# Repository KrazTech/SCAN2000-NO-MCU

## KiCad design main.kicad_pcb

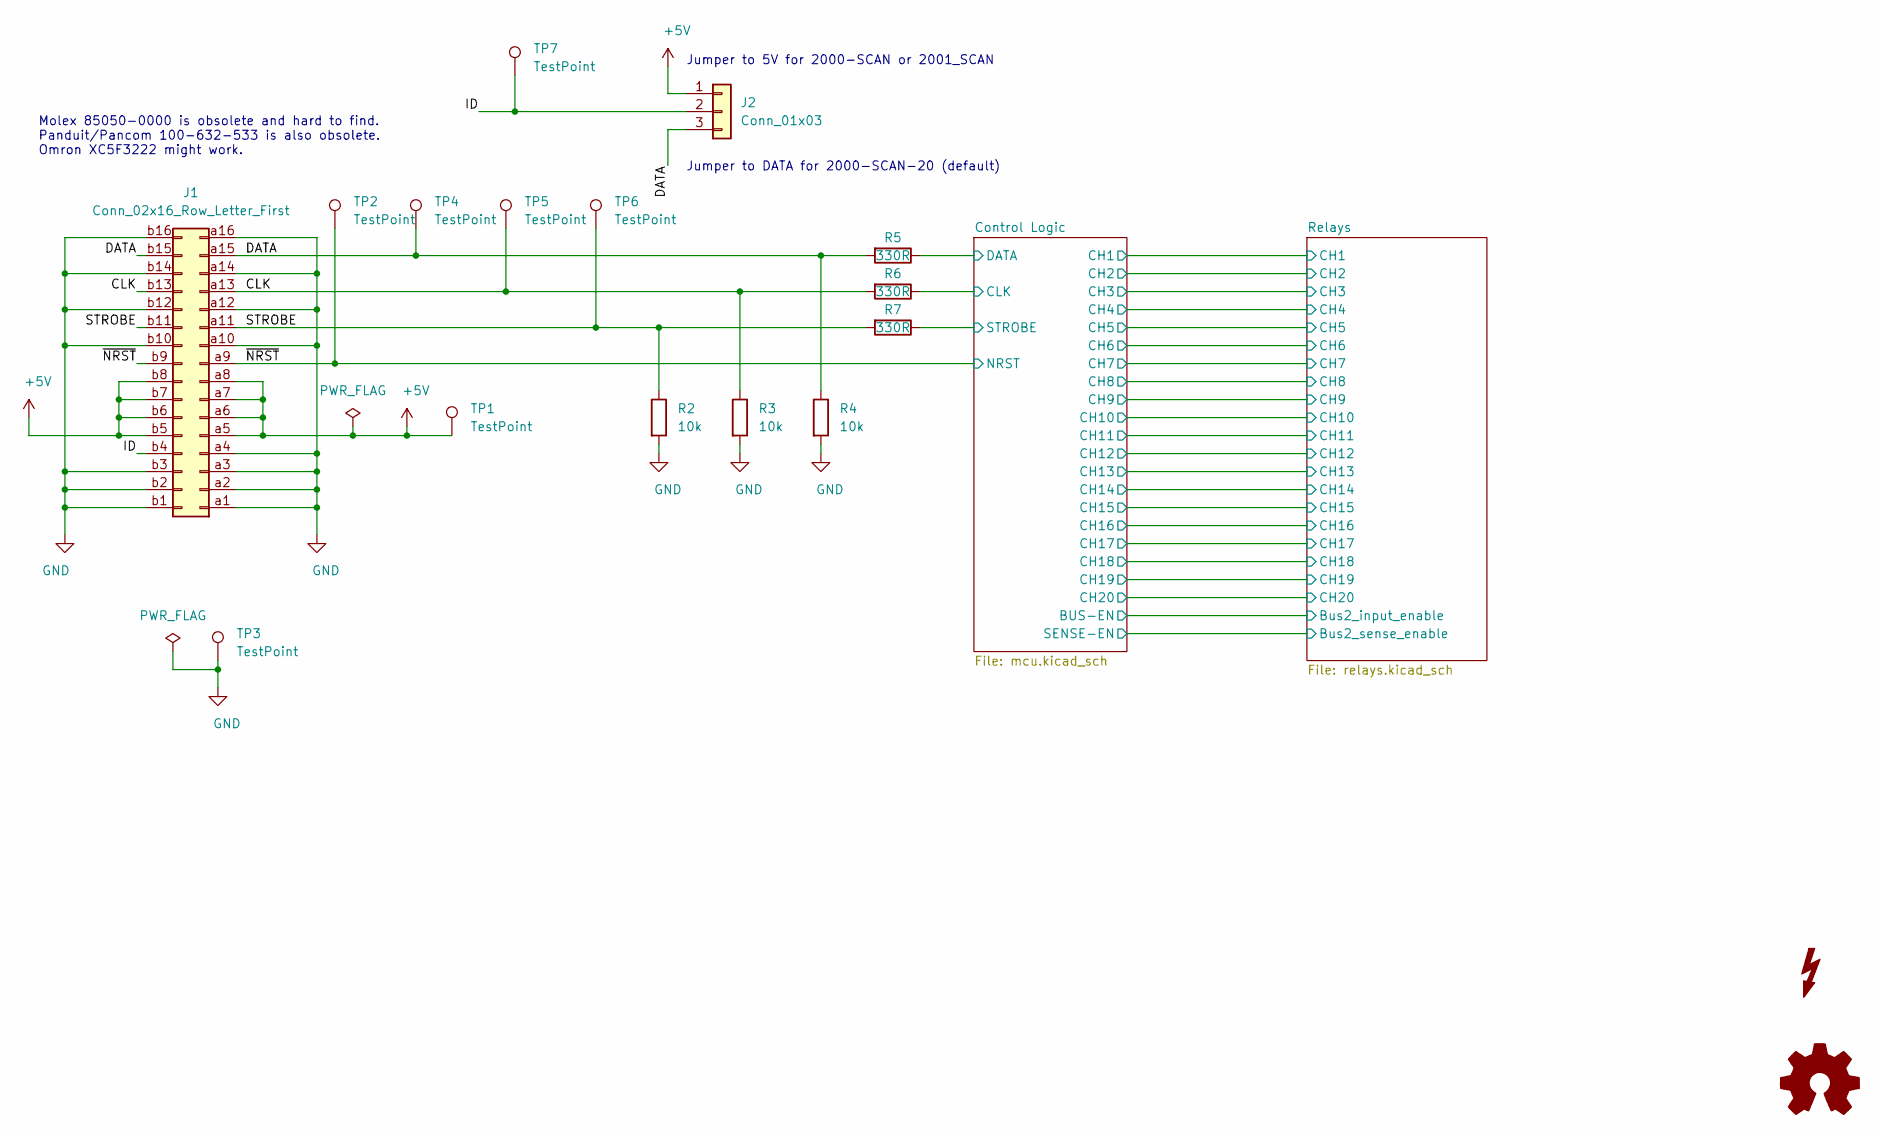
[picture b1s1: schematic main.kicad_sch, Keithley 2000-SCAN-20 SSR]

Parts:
J1: Conn_02x16_Row_Letter_First; DIN41612_B2_2x16_Male_Horizontal_THT
J2: Conn_01x03; PinHeader_1x03_P2.54mm_Vertical
LOGO2: Logo_Open_Hardware_Small; OSHW-Logo_7.5x8mm_SilkScreen
R2, R3, R4: 10k; R_0603_1608Metric
R5, R6, R7: 330R; R_0603_1608Metric
SYM1: SYM_Flash_Small; Symbol_Highvoltage_Type2_CopperTop_Small
TP1, TP2, TP3, TP4, TP5, TP6, TP7: TestPoint; TestPoint_Loop_D2.60mm_Drill1.6mm_Beaded

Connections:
+5V: J1.a5, J1.a6, J1.a7, J1.a8, J1.b5, J1.b6, J1.b7, J1.b8, J2.1, TP1.1; also elsewhere on the board
/CLK: J1.a13, J1.b13, R3.1, R6.2, TP5.1
/Control Logic/CLK: R6.1; also elsewhere on the board
/Control Logic/DATA: R5.1; also elsewhere on the board
/Control Logic/STROBE: R7.1; also elsewhere on the board
/DATA: J1.a15, J1.b15, J2.3, R4.1, R5.2, TP4.1
/ID: J1.b4, J2.2, TP7.1
/STROBE: J1.a11, J1.b11, R2.1, R7.2, TP6.1
/~NRST: J1.a9, J1.b9, TP2.1; also elsewhere on the board
GND: J1.a1, J1.a2, J1.a3, J1.a4, J1.a10, J1.a12, J1.a14, J1.a16, J1.b1, J1.b2, J1.b3, J1.b10, J1.b12, J1.b14, J1.b16, R2.2, R3.2, R4.2, TP3.1; also elsewhere on the board

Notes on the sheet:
Jumper to 5V for 2000-SCAN or 2001_SCAN
Molex 85050-0000 is obsolete and hard to find. Panduit/Pancom 100-632-533 is also obsolete. Omron XC5F3222 might work.
Jumper to DATA for 2000-SCAN-20 (default)

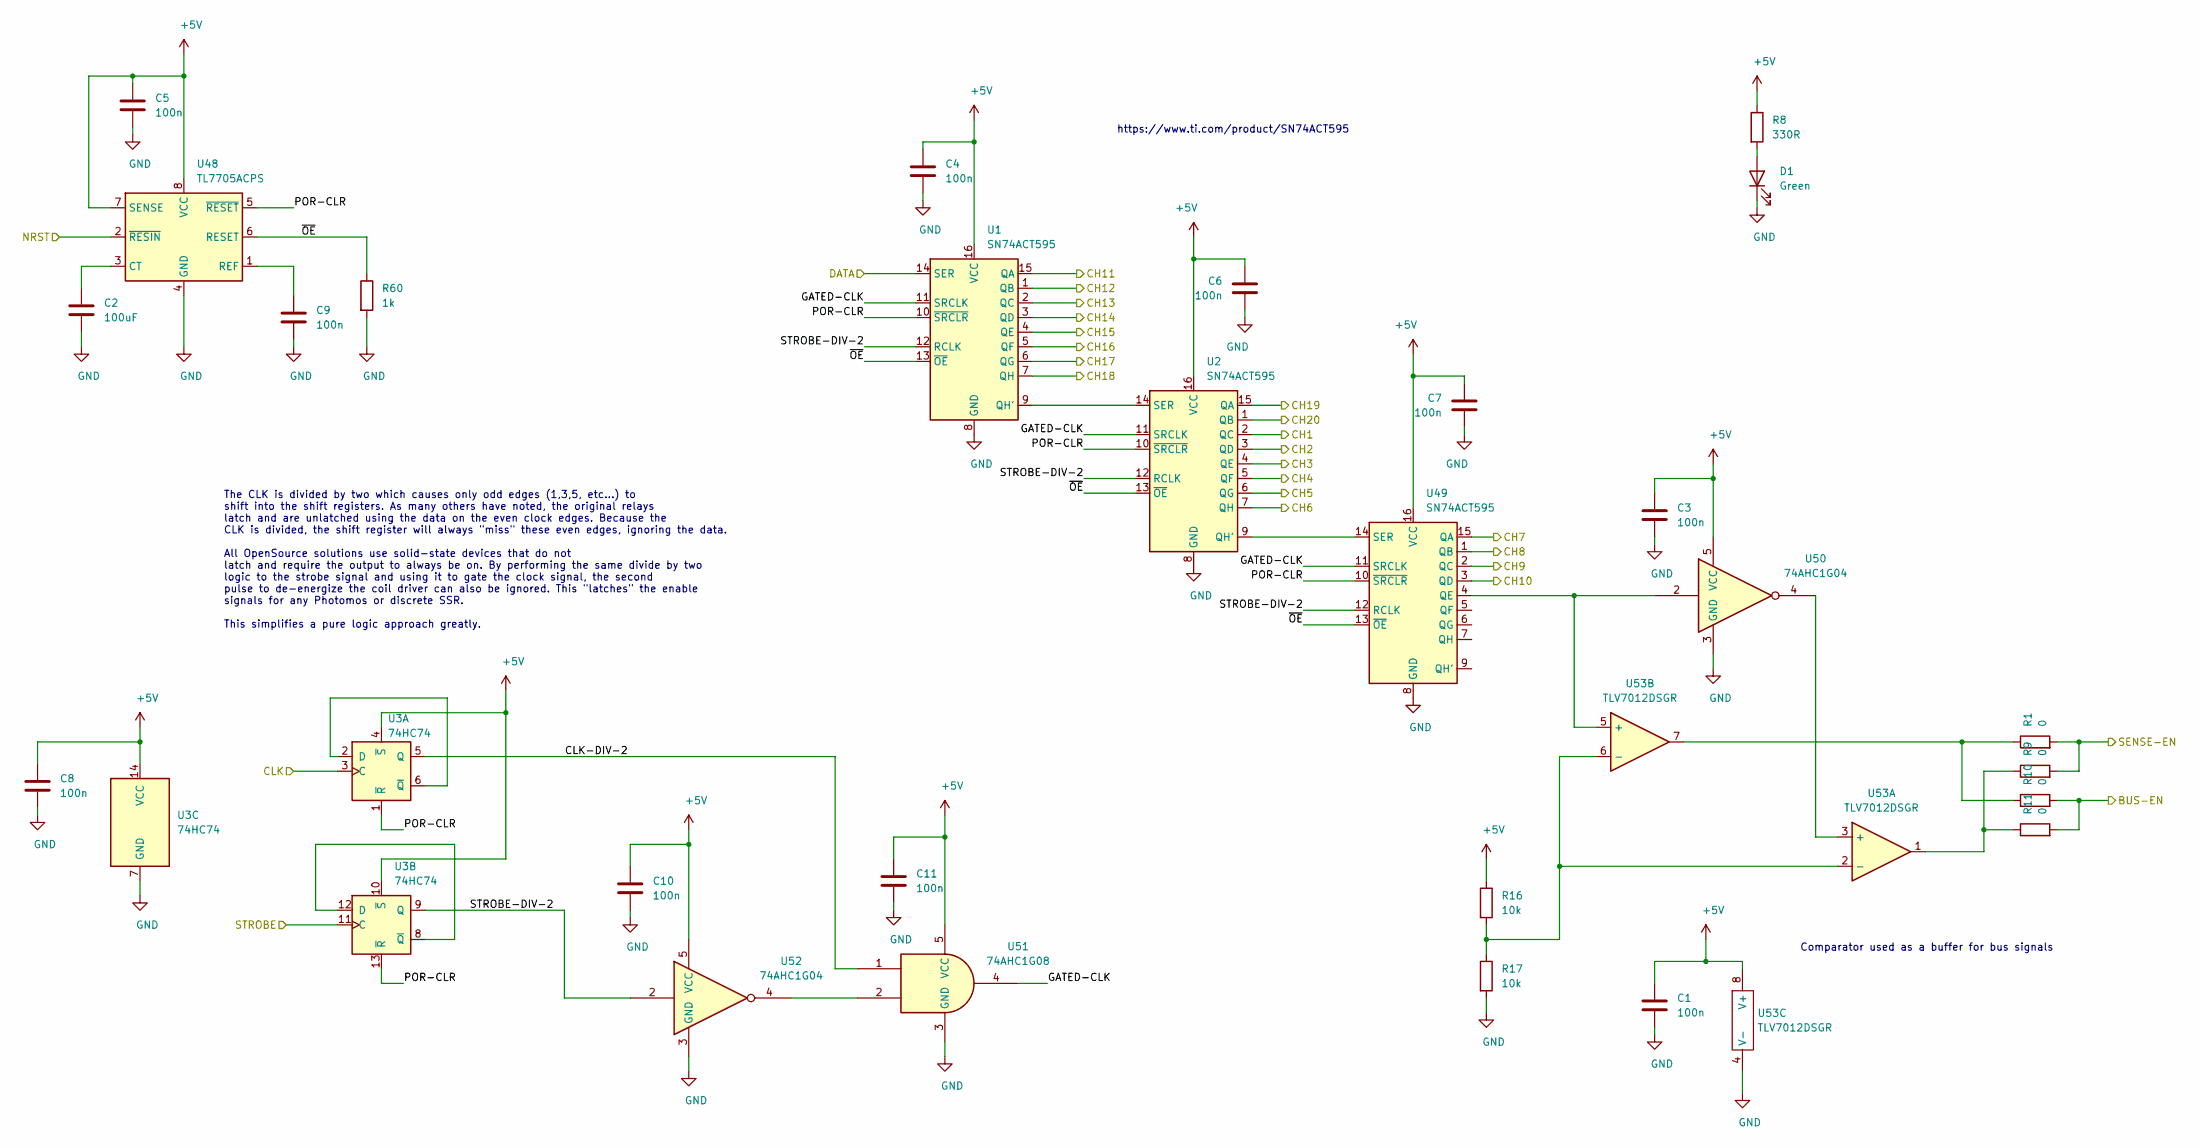
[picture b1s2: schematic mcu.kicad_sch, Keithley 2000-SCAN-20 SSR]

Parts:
C1, C3, C4, C5, C6, C7, C8, C9, C10, C11: 100n; C_0603_1608Metric
C2: 100uF; C_0603_1608Metric
D1: Green; LED_0603_1608Metric
R1, R9, R10, R11: 0; R_0603_1608Metric
R8: 330R; R_0603_1608Metric
R16, R17: 10k; R_0603_1608Metric
R60: 1k; R_0603_1608Metric
U1, U2, U49: SN74ACT595; TSSOP-16_4.4x5mm_P0.65mm
U3: 74HC74; TSSOP-14_4.4x5mm_P0.65mm
U48: TL7705ACPS; SOIC-8_5.3x6.2mm_P1.27mm
U50, U52: 74AHC1G04; SOT-553
U51: 74AHC1G08; SOT-553
U53: TLV7012DSGR; Texas_DSG0008A_WSON-8-1EP_2x2mm_P0.5mm_EP0.9x1.6mm_ThermalV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

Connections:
+5V: C1.1, C3.1, C4.1, C5.1, C6.1, C7.1, C8.1, C10.1, C11.1, R8.1, R16.1, U1.16 (VCC), U2.16 (VCC), U3.4 (~S), U3.10 (~S), U3.14 (VCC), U48.7 (SENSE), U48.8 (VCC), U49.16 (VCC), U50.5 (VCC), U51.5 (VCC), U52.5 (VCC), U53.8 (V+); also elsewhere on the board
/Control Logic/BUS-EN: R10.2, R11.2; also elsewhere on the board
/Control Logic/CH1: U2.2 (QC); also elsewhere on the board
/Control Logic/CH2: U2.3 (QD); also elsewhere on the board
/Control Logic/CH3: U2.4 (QE); also elsewhere on the board
/Control Logic/CH4: U2.5 (QF); also elsewhere on the board
/Control Logic/CH5: U2.6 (QG); also elsewhere on the board
/Control Logic/CH6: U2.7 (QH); also elsewhere on the board
/Control Logic/CH7: U49.15 (QA); also elsewhere on the board
/Control Logic/CH8: U49.1 (QB); also elsewhere on the board
/Control Logic/CH9: U49.2 (QC); also elsewhere on the board
/Control Logic/CH10: U49.3 (QD); also elsewhere on the board
/Control Logic/CH11: U1.15 (QA); also elsewhere on the board
/Control Logic/CH12: U1.1 (QB); also elsewhere on the board
/Control Logic/CH13: U1.2 (QC); also elsewhere on the board
/Control Logic/CH14: U1.3 (QD); also elsewhere on the board
/Control Logic/CH15: U1.4 (QE); also elsewhere on the board
/Control Logic/CH16: U1.5 (QF); also elsewhere on the board
/Control Logic/CH17: U1.6 (QG); also elsewhere on the board
/Control Logic/CH18: U1.7 (QH); also elsewhere on the board
/Control Logic/CH19: U2.15 (QA); also elsewhere on the board
/Control Logic/CH20: U2.1 (QB); also elsewhere on the board
/Control Logic/CLK: U3.3 (C); also elsewhere on the board
/Control Logic/CLK-DIV-2: U3.5 (Q), U51.1
/Control Logic/DATA: U1.14 (SER); also elsewhere on the board
/Control Logic/GATED-CLK: U1.11 (SRCLK), U2.11 (SRCLK), U49.11 (SRCLK), U51.4
/Control Logic/POR-CLR: U1.10 (~SRCLR), U2.10 (~SRCLR), U3.1 (~R), U3.13 (~R), U48.5 (~RESET), U49.10 (~SRCLR)
/Control Logic/SENSE-EN: R1.2, R9.2; also elsewhere on the board
/Control Logic/STROBE: U3.11 (C); also elsewhere on the board
/Control Logic/STROBE-DIV-2: U1.12 (RCLK), U2.12 (RCLK), U3.9 (Q), U49.12 (RCLK), U52.2
/Control Logic/~OE: R60.1, U1.13 (~OE), U2.13 (~OE), U48.6 (RESET), U49.13 (~OE)
/~NRST: U48.2 (~RESIN); also elsewhere on the board
GND: C1.2, C2.2, C3.2, C4.2, C5.2, C6.2, C7.2, C8.2, C9.2, C10.2, C11.2, D1.1 (K), R17.2, R60.2, U1.8 (GND), U2.8 (GND), U3.7 (GND), U48.4 (GND), U49.8 (GND), U50.3 (GND), U51.3 (GND), U52.3 (GND), U53.4 (V-); also elsewhere on the board
unnamed: D1.2 (A), R8.2
unnamed: R1.1, R10.1, U53.7
unnamed: R9.1, R11.1, U53.1
unnamed: U1.9 (QH'), U2.14 (SER)
unnamed: U2.9 (QH'), U49.14 (SER)
unnamed: U3.2 (D), U3.6 (~Q)
unnamed: U3.8 (~Q), U3.12 (D)
unnamed: C2.1, U48.3 (CT)
unnamed: C9.1, U48.1 (REF)
unnamed: U49.4 (QE), U50.2, U53.5 (+)
unnamed: U51.2, U52.4
unnamed: U50.4, U53.3 (+)
unnamed: R16.2, R17.1, U53.2 (-), U53.6 (-)

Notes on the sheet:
The CLK is divided by two which causes only odd edges (1,3,5, etc...) to shift into the shift registers. As many others have noted, the original relays latch and are unlatched using the data on the even clock edges. Because the CLK is divided, the shift register will always "miss" these even edges,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
https://www.ti.com/product/SN74ACT595
Comparator used as a buffer for bus signals

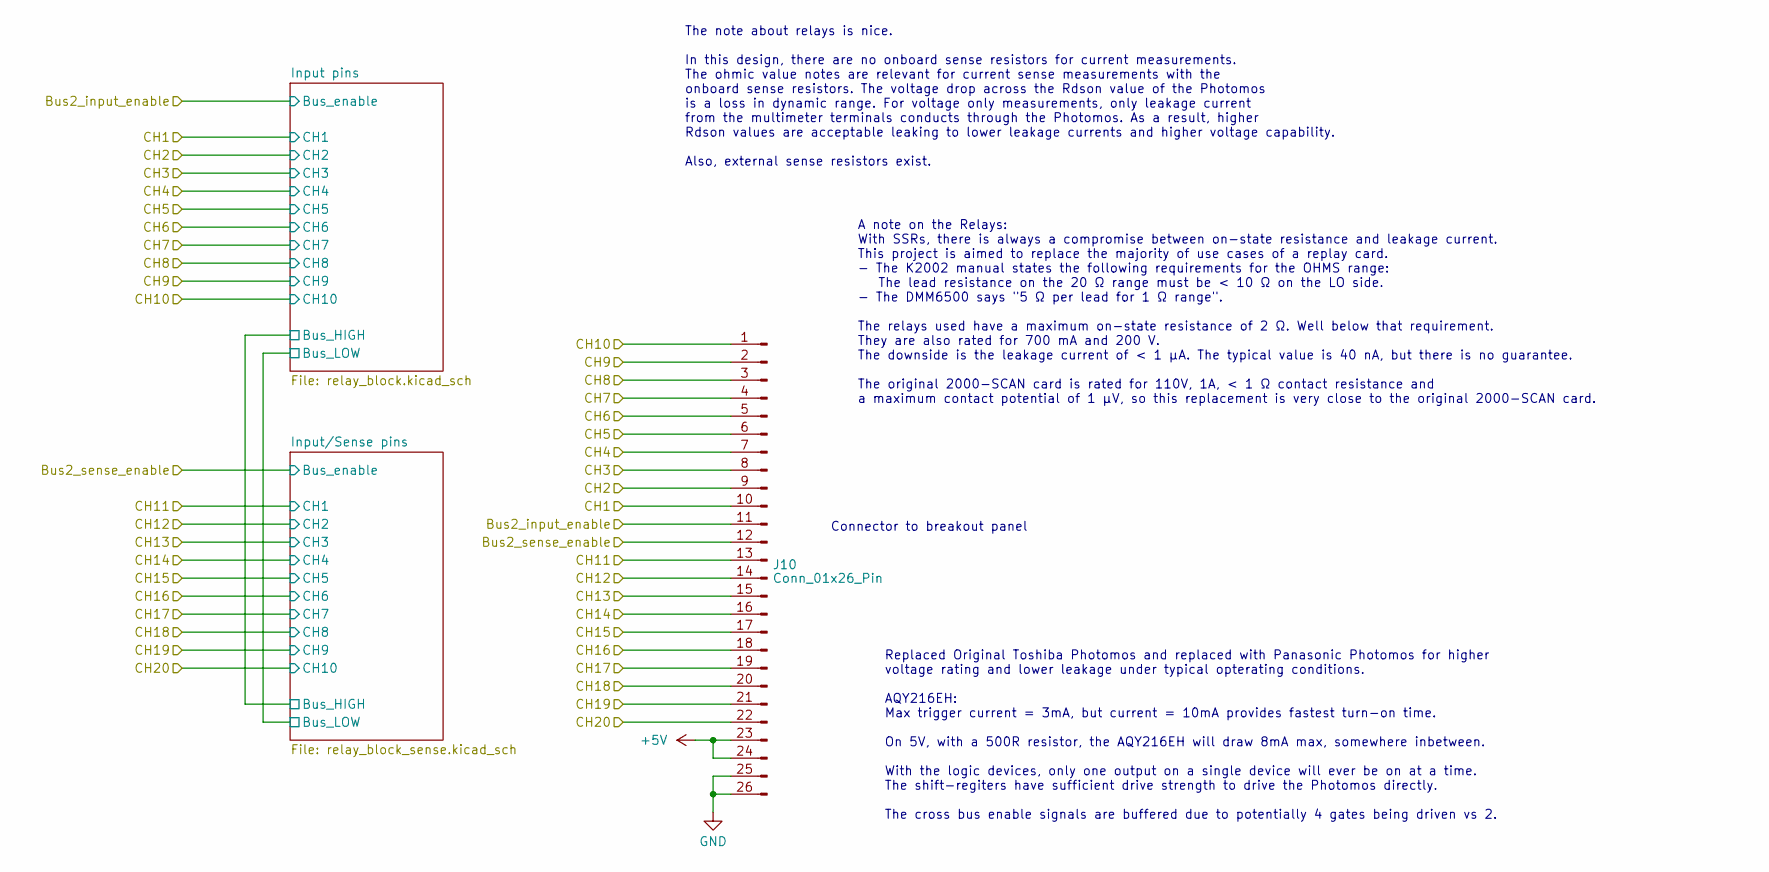
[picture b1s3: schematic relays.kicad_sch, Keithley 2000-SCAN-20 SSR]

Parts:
J10: Conn_01x26_Pin; IDC-Header_2x13_P2.54mm_Latch_Horizontal

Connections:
+5V: J10.23, J10.24; also elsewhere on the board
/Control Logic/BUS-EN: J10.11; also elsewhere on the board
/Control Logic/CH1: J10.10; also elsewhere on the board
/Control Logic/CH2: J10.9; also elsewhere on the board
/Control Logic/CH3: J10.8; also elsewhere on the board
/Control Logic/CH4: J10.7; also elsewhere on the board
/Control Logic/CH5: J10.6; also elsewhere on the board
/Control Logic/CH6: J10.5; also elsewhere on the board
/Control Logic/CH7: J10.4; also elsewhere on the board
/Control Logic/CH8: J10.3; also elsewhere on the board
/Control Logic/CH9: J10.2; also elsewhere on the board
/Control Logic/CH10: J10.1; also elsewhere on the board
/Control Logic/CH11: J10.13; also elsewhere on the board
/Control Logic/CH12: J10.14; also elsewhere on the board
/Control Logic/CH13: J10.15; also elsewhere on the board
/Control Logic/CH14: J10.16; also elsewhere on the board
/Control Logic/CH15: J10.17; also elsewhere on the board
/Control Logic/CH16: J10.18; also elsewhere on the board
/Control Logic/CH17: J10.19; also elsewhere on the board
/Control Logic/CH18: J10.20; also elsewhere on the board
/Control Logic/CH19: J10.21; also elsewhere on the board
/Control Logic/CH20: J10.22; also elsewhere on the board
/Control Logic/SENSE-EN: J10.12; also elsewhere on the board
GND: J10.25, J10.26; also elsewhere on the board

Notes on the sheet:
A note on the Relays: With SSRs, there is always a compromise between on-state resistance and leakage current. This project is aimed to replace the majority of use cases of a replay card. - The K2002 manual states the following requirements for the OHMS range: The lead resistance on the 20 Ω range 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
Replaced Original Toshiba Photomos and replaced with Panasonic Photomos for higher voltage rating and lower leakage under typical opterating conditions. AQY216EH: Max trigger current = 3mA, but current = 10mA provides fastest turn-on time. On 5V, with a 500R resistor, the AQY216EH will draw 8mA max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
The note about relays is nice. In this design, there are no onboard sense resistors for current measurements. The ohmic value notes are relevant for current sense measurements with the onboard sense resistors. The voltage drop across the Rdson value of the Photomos is a loss in dynamic range. For v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
Connector to breakout panel

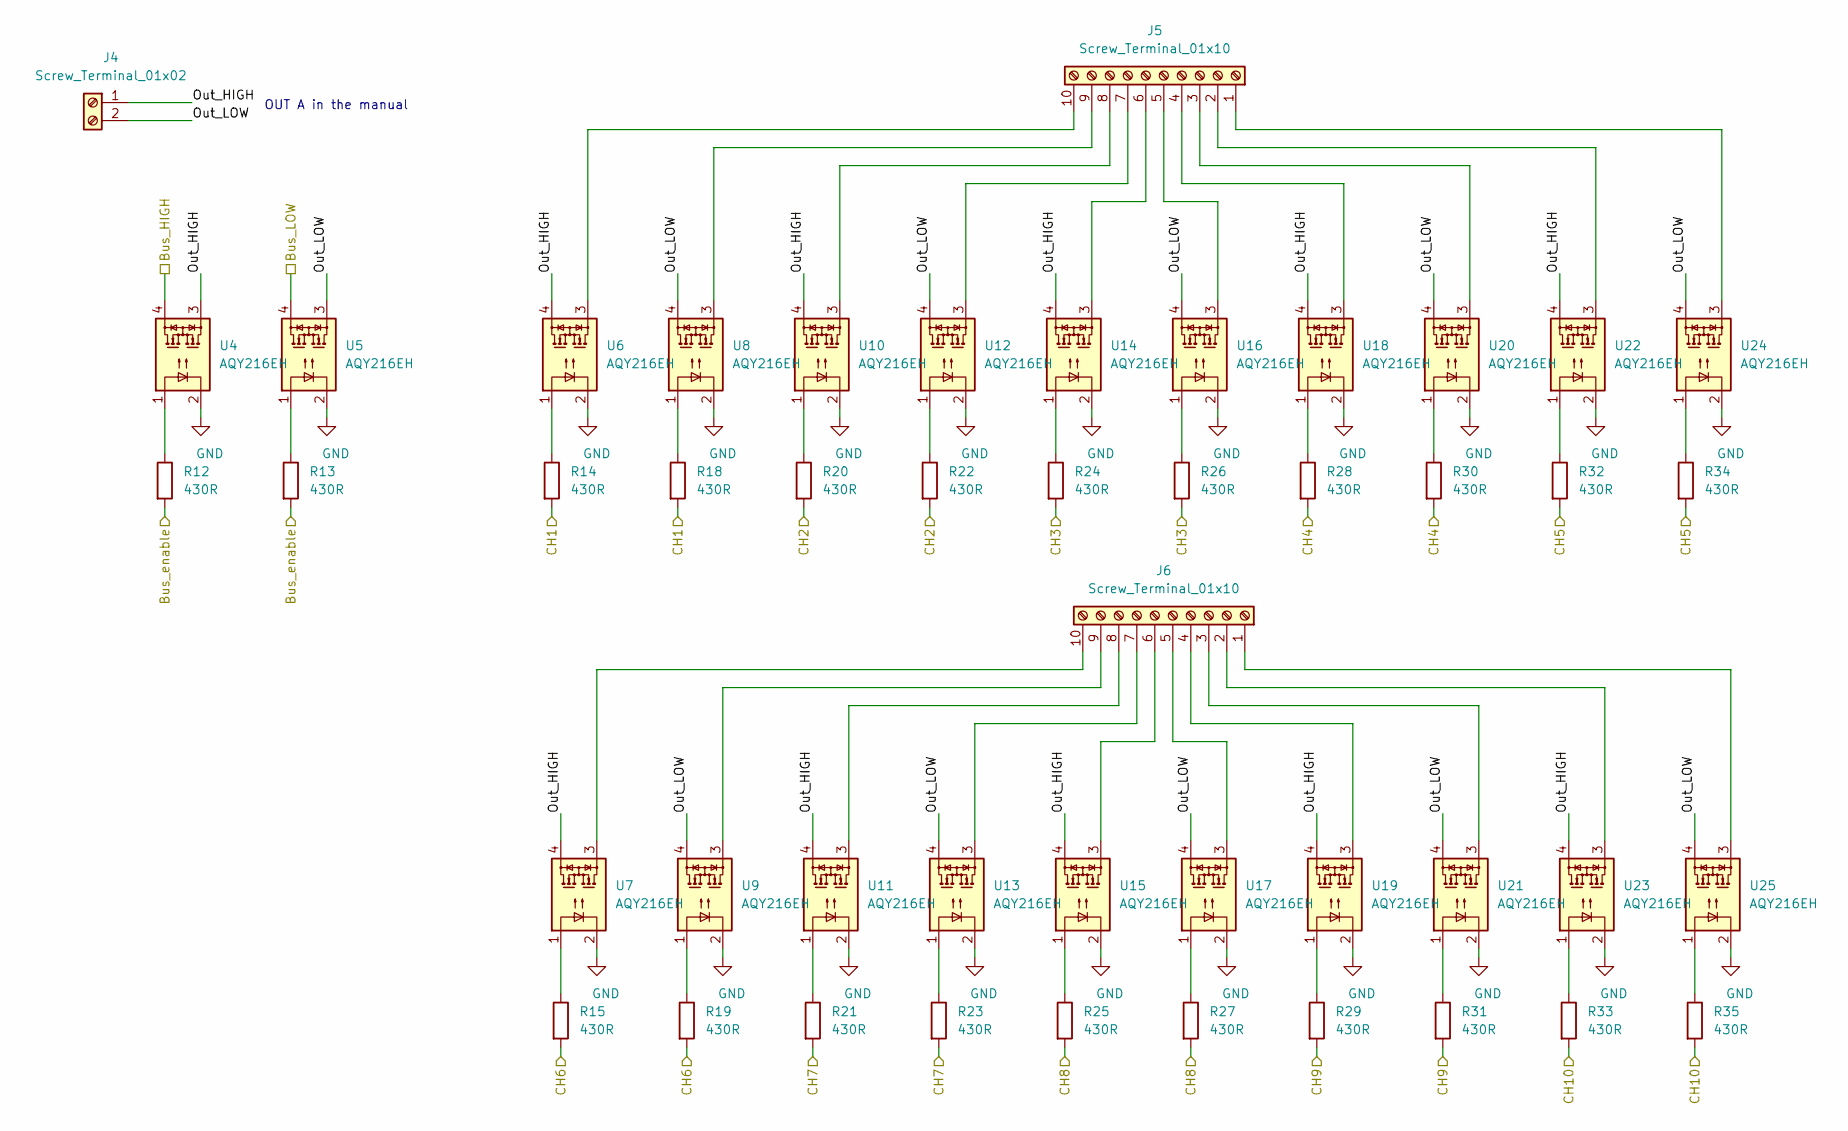
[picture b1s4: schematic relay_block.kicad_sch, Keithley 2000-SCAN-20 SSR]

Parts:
J4: Screw_Terminal_01x02; TerminalBlock_Phoenix_SMKDSN-1,5-2-5.08_1x02_P5.08mm_Horizo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
J5, J6: Screw_Terminal_01x10; TerminalBlock_Phoenix_SMKDSN-1,5-10-5.08_1x10_P5.08mm_Horiz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
R12, R13, R14, R15, R18, R19, R20, R21, R22, R23, R24, R25, R26, R27, R28, R29, R30, R31, R32, R33, R34, R35: 430R; R_0603_1608Metric
U4, U5, U6, U7, U8, U9, U10, U11, U12, U13, U14, U15, U16, U17, U18, U19, U20, U21, U22, U23, U24, U25: AQY216EH; DIP-4_W7.62mm_Least

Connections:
/Control Logic/BUS-EN: R12.2, R13.2; also elsewhere on the board
/Control Logic/CH1: R14.2, R18.2; also elsewhere on the board
/Control Logic/CH2: R20.2, R22.2; also elsewhere on the board
/Control Logic/CH3: R24.2, R26.2; also elsewhere on the board
/Control Logic/CH4: R28.2, R30.2; also elsewhere on the board
/Control Logic/CH5: R32.2, R34.2; also elsewhere on the board
/Control Logic/CH6: R15.2, R19.2; also elsewhere on the board
/Control Logic/CH7: R21.2, R23.2; also elsewhere on the board
/Control Logic/CH8: R25.2, R27.2; also elsewhere on the board
/Control Logic/CH9: R29.2, R31.2; also elsewhere on the board
/Control Logic/CH10: R33.2, R35.2; also elsewhere on the board
/Relays/Input pins/Bus_HIGH: U4.4; also elsewhere on the board
/Relays/Input pins/Bus_LOW: U5.4; also elsewhere on the board
/Relays/Input pins/Out_HIGH: J4.1, U4.3, U6.4, U7.4, U10.4, U11.4, U14.4, U15.4, U18.4, U19.4, U22.4, U23.4
/Relays/Input pins/Out_LOW: J4.2, U5.3, U8.4, U9.4, U12.4, U13.4, U16.4, U17.4, U20.4, U21.4, U24.4, U25.4
GND: U4.2, U5.2, U6.2, U7.2, U8.2, U9.2, U10.2, U11.2, U12.2, U13.2, U14.2, U15.2, U16.2, U17.2, U18.2, U19.2, U20.2, U21.2, U22.2, U23.2, U24.2, U25.2; also elsewhere on the board
unnamed: J5.1, U24.3
unnamed: J5.2, U22.3
unnamed: J5.3, U20.3
unnamed: J5.4, U18.3
unnamed: J5.5, U16.3
unnamed: J5.6, U14.3
unnamed: J5.7, U12.3
unnamed: J5.8, U10.3
unnamed: J5.9, U8.3
unnamed: J5.10, U6.3
unnamed: J6.1, U25.3
unnamed: J6.2, U23.3
unnamed: J6.3, U21.3
unnamed: J6.4, U19.3
unnamed: J6.5, U17.3
unnamed: J6.6, U15.3
unnamed: J6.7, U13.3
unnamed: J6.8, U11.3
unnamed: J6.9, U9.3
unnamed: J6.10, U7.3
unnamed: R12.1, U4.1
unnamed: R13.1, U5.1
unnamed: R14.1, U6.1
unnamed: R15.1, U7.1
unnamed: R18.1, U8.1
unnamed: R19.1, U9.1
unnamed: R20.1, U10.1
unnamed: R21.1, U11.1
unnamed: R22.1, U12.1
unnamed: R23.1, U13.1
unnamed: R24.1, U14.1
unnamed: R25.1, U15.1
unnamed: R26.1, U16.1
unnamed: R27.1, U17.1
unnamed: R28.1, U18.1
unnamed: R29.1, U19.1
unnamed: R30.1, U20.1
unnamed: R31.1, U21.1
unnamed: R32.1, U22.1
unnamed: R33.1, U23.1
unnamed: R34.1, U24.1
unnamed: R35.1, U25.1

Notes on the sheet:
OUT A in the manual

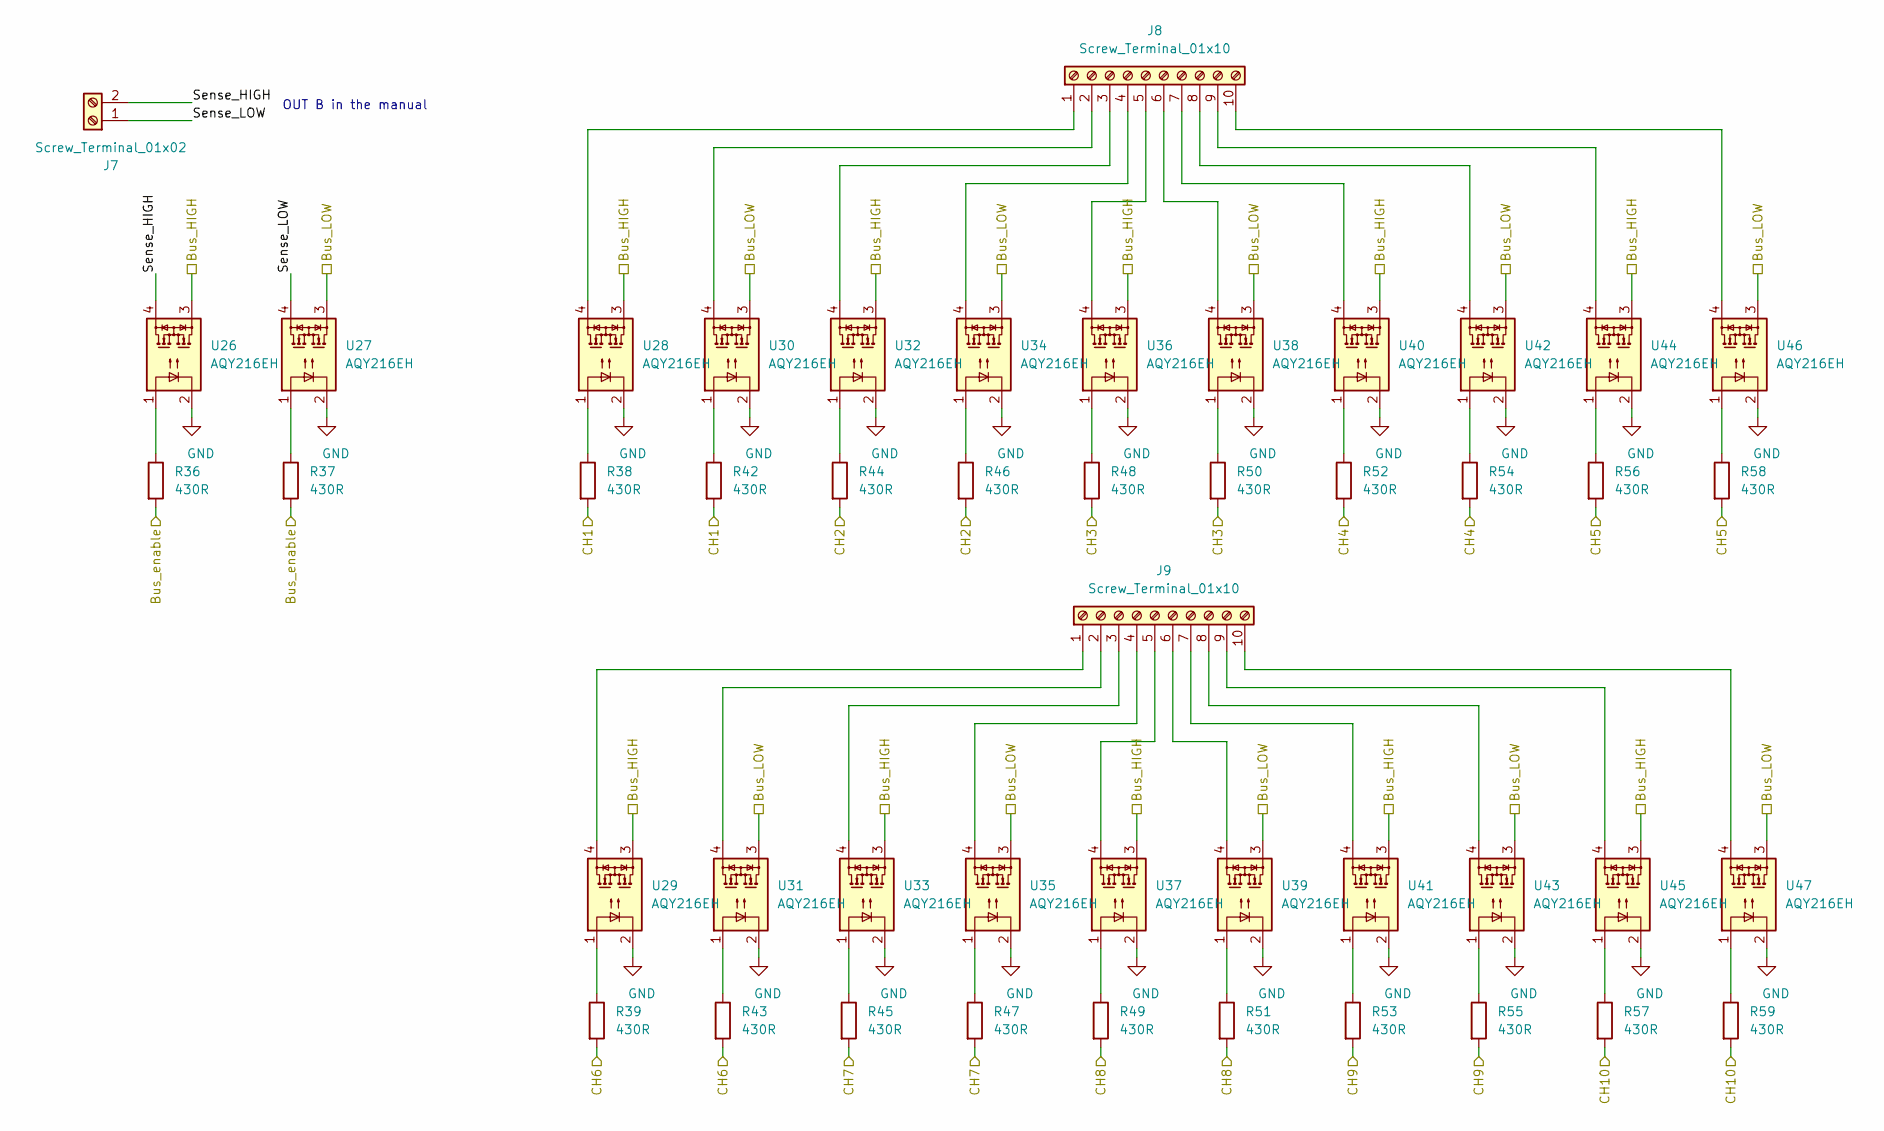
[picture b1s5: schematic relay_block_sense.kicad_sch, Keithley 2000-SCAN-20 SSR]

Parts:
J7: Screw_Terminal_01x02; TerminalBlock_Phoenix_SMKDSN-1,5-2-5.08_1x02_P5.08mm_Horizo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
J8, J9: Screw_Terminal_01x10; TerminalBlock_Phoenix_SMKDSN-1,5-10-5.08_1x10_P5.08mm_Horiz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
R36, R37, R38, R39, R42, R43, R44, R45, R46, R47, R48, R49, R50, R51, R52, R53, R54, R55, R56, R57, R58, R59: 430R; R_0603_1608Metric
U26, U27, U28, U29, U30, U31, U32, U33, U34, U35, U36, U37, U38, U39, U40, U41, U42, U43, U44, U45, U46, U47: AQY216EH; DIP-4_W7.62mm_Least

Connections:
/Control Logic/CH11: R38.2, R42.2; also elsewhere on the board
/Control Logic/CH12: R44.2, R46.2; also elsewhere on the board
/Control Logic/CH13: R48.2, R50.2; also elsewhere on the board
/Control Logic/CH14: R52.2, R54.2; also elsewhere on the board
/Control Logic/CH15: R56.2, R58.2; also elsewhere on the board
/Control Logic/CH16: R39.2, R43.2; also elsewhere on the board
/Control Logic/CH17: R45.2, R47.2; also elsewhere on the board
/Control Logic/CH18: R49.2, R51.2; also elsewhere on the board
/Control Logic/CH19: R53.2, R55.2; also elsewhere on the board
/Control Logic/CH20: R57.2, R59.2; also elsewhere on the board
/Control Logic/SENSE-EN: R36.2, R37.2; also elsewhere on the board
/Relays/Input pins/Bus_HIGH: U26.3, U28.3, U29.3, U32.3, U33.3, U36.3, U37.3, U40.3, U41.3, U44.3, U45.3; also elsewhere on the board
/Relays/Input pins/Bus_LOW: U27.3, U30.3, U31.3, U34.3, U35.3, U38.3, U39.3, U42.3, U43.3, U46.3, U47.3; also elsewhere on the board
/Relays/Input/Sense pins/Sense_HIGH: J7.2, U26.4
/Relays/Input/Sense pins/Sense_LOW: J7.1, U27.4
GND: U26.2, U27.2, U28.2, U29.2, U30.2, U31.2, U32.2, U33.2, U34.2, U35.2, U36.2, U37.2, U38.2, U39.2, U40.2, U41.2, U42.2, U43.2, U44.2, U45.2, U46.2, U47.2; also elsewhere on the board
unnamed: J8.1, U28.4
unnamed: J8.2, U30.4
unnamed: J8.3, U32.4
unnamed: J8.4, U34.4
unnamed: J8.5, U36.4
unnamed: J8.6, U38.4
unnamed: J8.7, U40.4
unnamed: J8.8, U42.4
unnamed: J8.9, U44.4
unnamed: J8.10, U46.4
unnamed: J9.1, U29.4
unnamed: J9.2, U31.4
unnamed: J9.3, U33.4
unnamed: J9.4, U35.4
unnamed: J9.5, U37.4
unnamed: J9.6, U39.4
unnamed: J9.7, U41.4
unnamed: J9.8, U43.4
unnamed: J9.9, U45.4
unnamed: J9.10, U47.4
unnamed: R36.1, U26.1
unnamed: R37.1, U27.1
unnamed: R38.1, U28.1
unnamed: R39.1, U29.1
unnamed: R42.1, U30.1
unnamed: R43.1, U31.1
unnamed: R44.1, U32.1
unnamed: R45.1, U33.1
unnamed: R46.1, U34.1
unnamed: R47.1, U35.1
unnamed: R48.1, U36.1
unnamed: R49.1, U37.1
unnamed: R50.1, U38.1
unnamed: R51.1, U39.1
unnamed: R52.1, U40.1
unnamed: R53.1, U41.1
unnamed: R54.1, U42.1
unnamed: R55.1, U43.1
unnamed: R56.1, U44.1
unnamed: R57.1, U45.1
unnamed: R58.1, U46.1
unnamed: R59.1, U47.1

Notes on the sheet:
OUT B in the manual

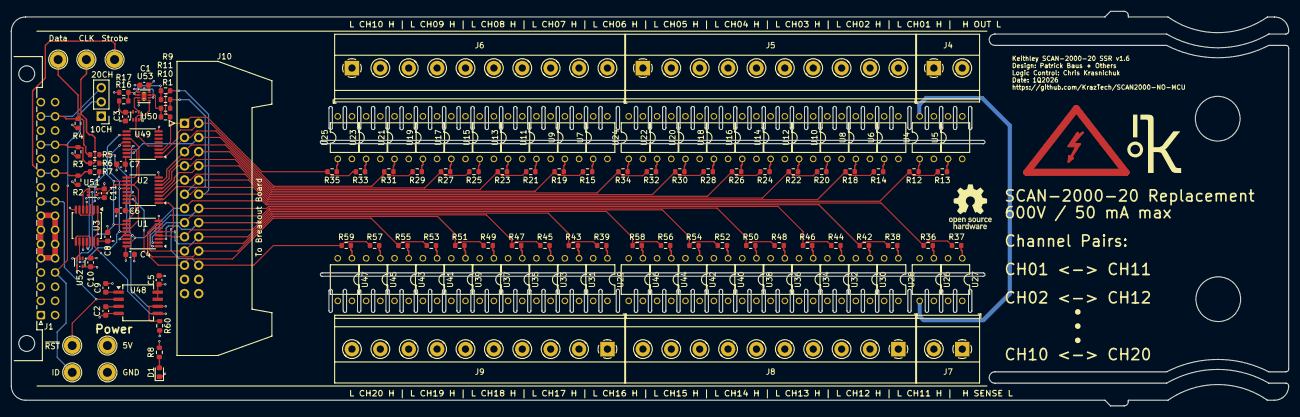
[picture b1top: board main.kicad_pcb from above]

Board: 4 copper layers, 228.6 x 70.6 mm, 141 parts (0 on the bottom side), 140 nets.

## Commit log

2026-03-02 Version 1.6
    Created a high-voltage rated scan board.
    Control is done completely in logic to avoid programming an MCU
2026-03-02 Added Image

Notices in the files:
main.kicad_pcb:
Copyright (©) 2021, Patrick Baus
Licensed under CERN OHL v.1.2
mcu.kicad_sch:
Copyright (©) 2026, Chris Krasnichuk
